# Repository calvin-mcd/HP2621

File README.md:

# HP2621

A pcb based on the HP2621 vintage home computer, supporting both MX and Alps switches and an extensive bottomrow.

Two case designs are being worked on by @obobobobo and fivedee.

## Layout

[Link](http://www.keyboard-layout-editor.com/#/gists/fb3fb2c8d70fd99746aac4b5d0be48f5)

## Pictures

The OG keyboard/computer inspiration

## Todo

- [ ] order & test pcb
- [ ] create firmware
- [ ] create & test cases

## Disclaimer

Please note that this project is a work in progress with no guarantees of a working outcome. No-one involved in this project is responsible for any usage issues that may arise. However, feel free to edit, modify and otherwise utilise these files.

## License

This project is released under the GPL v3 License. Please refer to the LICENCE file.

## Credits

Any questions, contact Calvin0563 on Discord.

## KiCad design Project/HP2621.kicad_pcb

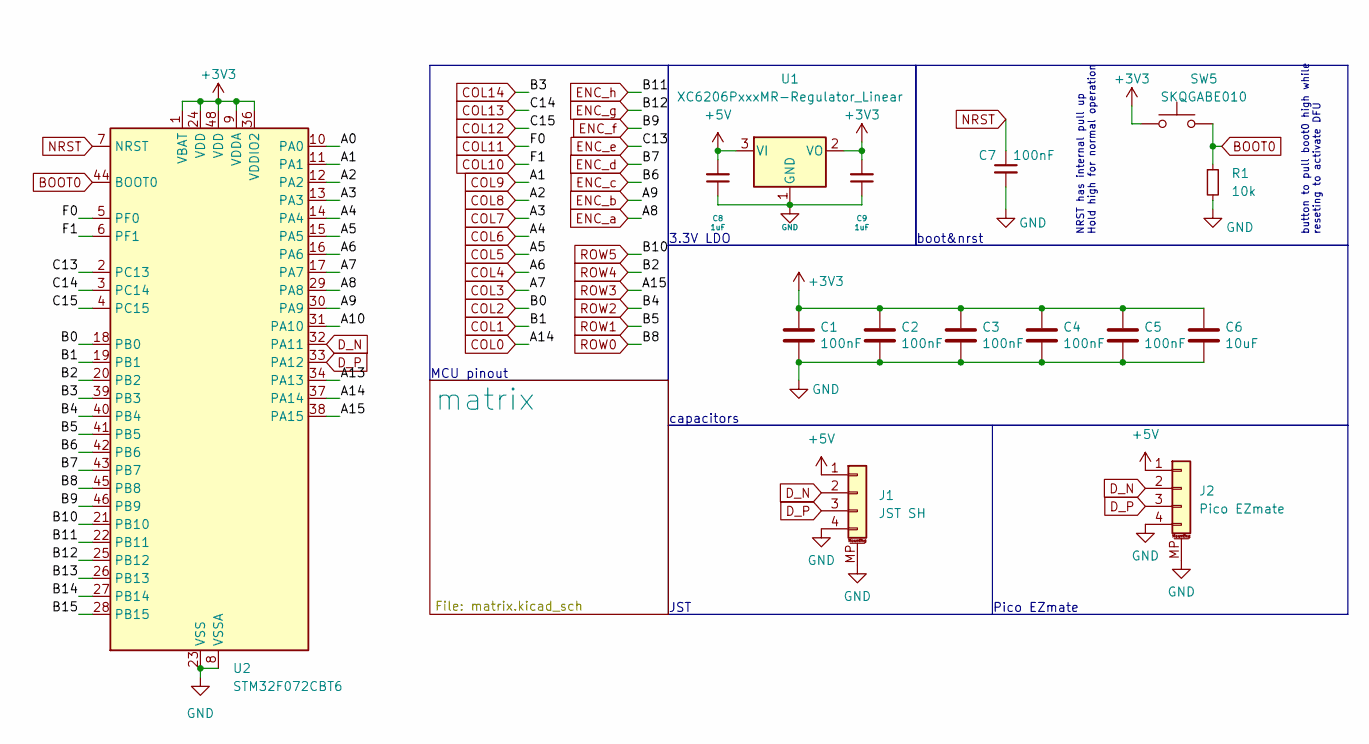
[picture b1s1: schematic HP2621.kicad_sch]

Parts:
C1, C2, C3, C4, C5, C7: 100nF; C_0402_1005Metric; LCSC C307331
C6: 10uF; C_0603_1608Metric
C8, C9: 1uF; C_0402_1005Metric; LCSC C52923
J1: JST SH; JST_SH_SM04B-SRSS-TB_1x04-1MP_P1.00mm_Horizontal
J2: Pico EZmate; Molex_Pico-EZmate_78171-0004_1x04-1MP_P1.20mm_Vertical
R1: 10k; R_0402_1005Metric
SW5: SKQGABE010; SW_SPST_SKQG_WithStem; LCSC C115351
U1: XC6206PxxxMR-Regulator_Linear; SOT-23; LCSC C5446
U2: STM32F072CBT6; LQFP-48_7x7mm_P0.5mm; JlcRotOffset 90

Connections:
+3V3: C1.1, C2.1, C3.1, C4.1, C5.1, C6.1, C9.2, SW5.1, U1.2 (VO), U2.1 (VBAT), U2.9 (VDDA), U2.24 (VDD), U2.36 (VDDIO2), U2.48 (VDD)
+5V: C8.2, J1.1, J2.1, U1.3 (VI)
/A0: U2.10 (PA0)
/A10: U2.31 (PA10)
/A13: U2.34 (PA13)
/B13: U2.26 (PB13)
/B14: U2.27 (PB14)
/B15: U2.28 (PB15)
BOOT0: R1.1, SW5.2, U2.44 (BOOT0)
COL0: U2.37 (PA14); also elsewhere on the board
COL1: U2.19 (PB1); also elsewhere on the board
COL2: U2.18 (PB0); also elsewhere on the board
COL3: U2.17 (PA7); also elsewhere on the board
COL4: U2.16 (PA6); also elsewhere on the board
COL5: U2.15 (PA5); also elsewhere on the board
COL6: U2.14 (PA4); also elsewhere on the board
COL7: U2.13 (PA3); also elsewhere on the board
COL8: U2.12 (PA2); also elsewhere on the board
COL9: U2.11 (PA1); also elsewhere on the board
COL10: U2.6 (PF1); also elsewhere on the board
COL11: U2.5 (PF0); also elsewhere on the board
COL12: U2.4 (PC15); also elsewhere on the board
COL13: U2.3 (PC14); also elsewhere on the board
COL14: U2.39 (PB3); also elsewhere on the board
D_N: J1.2, J2.2, U2.32 (PA11)
D_P: J1.3, J2.3, U2.33 (PA12)
ENC_a: U2.29 (PA8); also elsewhere on the board
ENC_b: U2.30 (PA9); also elsewhere on the board
ENC_c: U2.42 (PB6); also elsewhere on the board
ENC_d: U2.43 (PB7); also elsewhere on the board
ENC_e: U2.2 (PC13); also elsewhere on the board
ENC_f: U2.46 (PB9); also elsewhere on the board
ENC_g: U2.25 (PB12); also elsewhere on the board
ENC_h: U2.22 (PB11); also elsewhere on the board
GND: C1.2, C2.2, C3.2, C4.2, C5.2, C6.2, C7.2, C8.1, C9.1, J1.4, J1.MP (MountPin), J2.4, J2.MP (MountPin), R1.2, U1.1 (GND), U2.8 (VSSA), U2.23 (VSS), U2.35 (VSS), U2.47 (VSS); also elsewhere on the board
NRST: C7.1, U2.7 (NRST)
ROW0: U2.45 (PB8); also elsewhere on the board
ROW1: U2.41 (PB5); also elsewhere on the board
ROW2: U2.40 (PB4); also elsewhere on the board
ROW3: U2.38 (PA15); also elsewhere on the board
ROW4: U2.20 (PB2); also elsewhere on the board
ROW5: U2.21 (PB10); also elsewhere on the board

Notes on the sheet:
3.3V LDO
capacitors
NRST has internal pull up Hold high for normal operation
boot&nrst
MCU pinout
Pico EZmate
JST
button to pull boot0 high while reseting to activate DFU

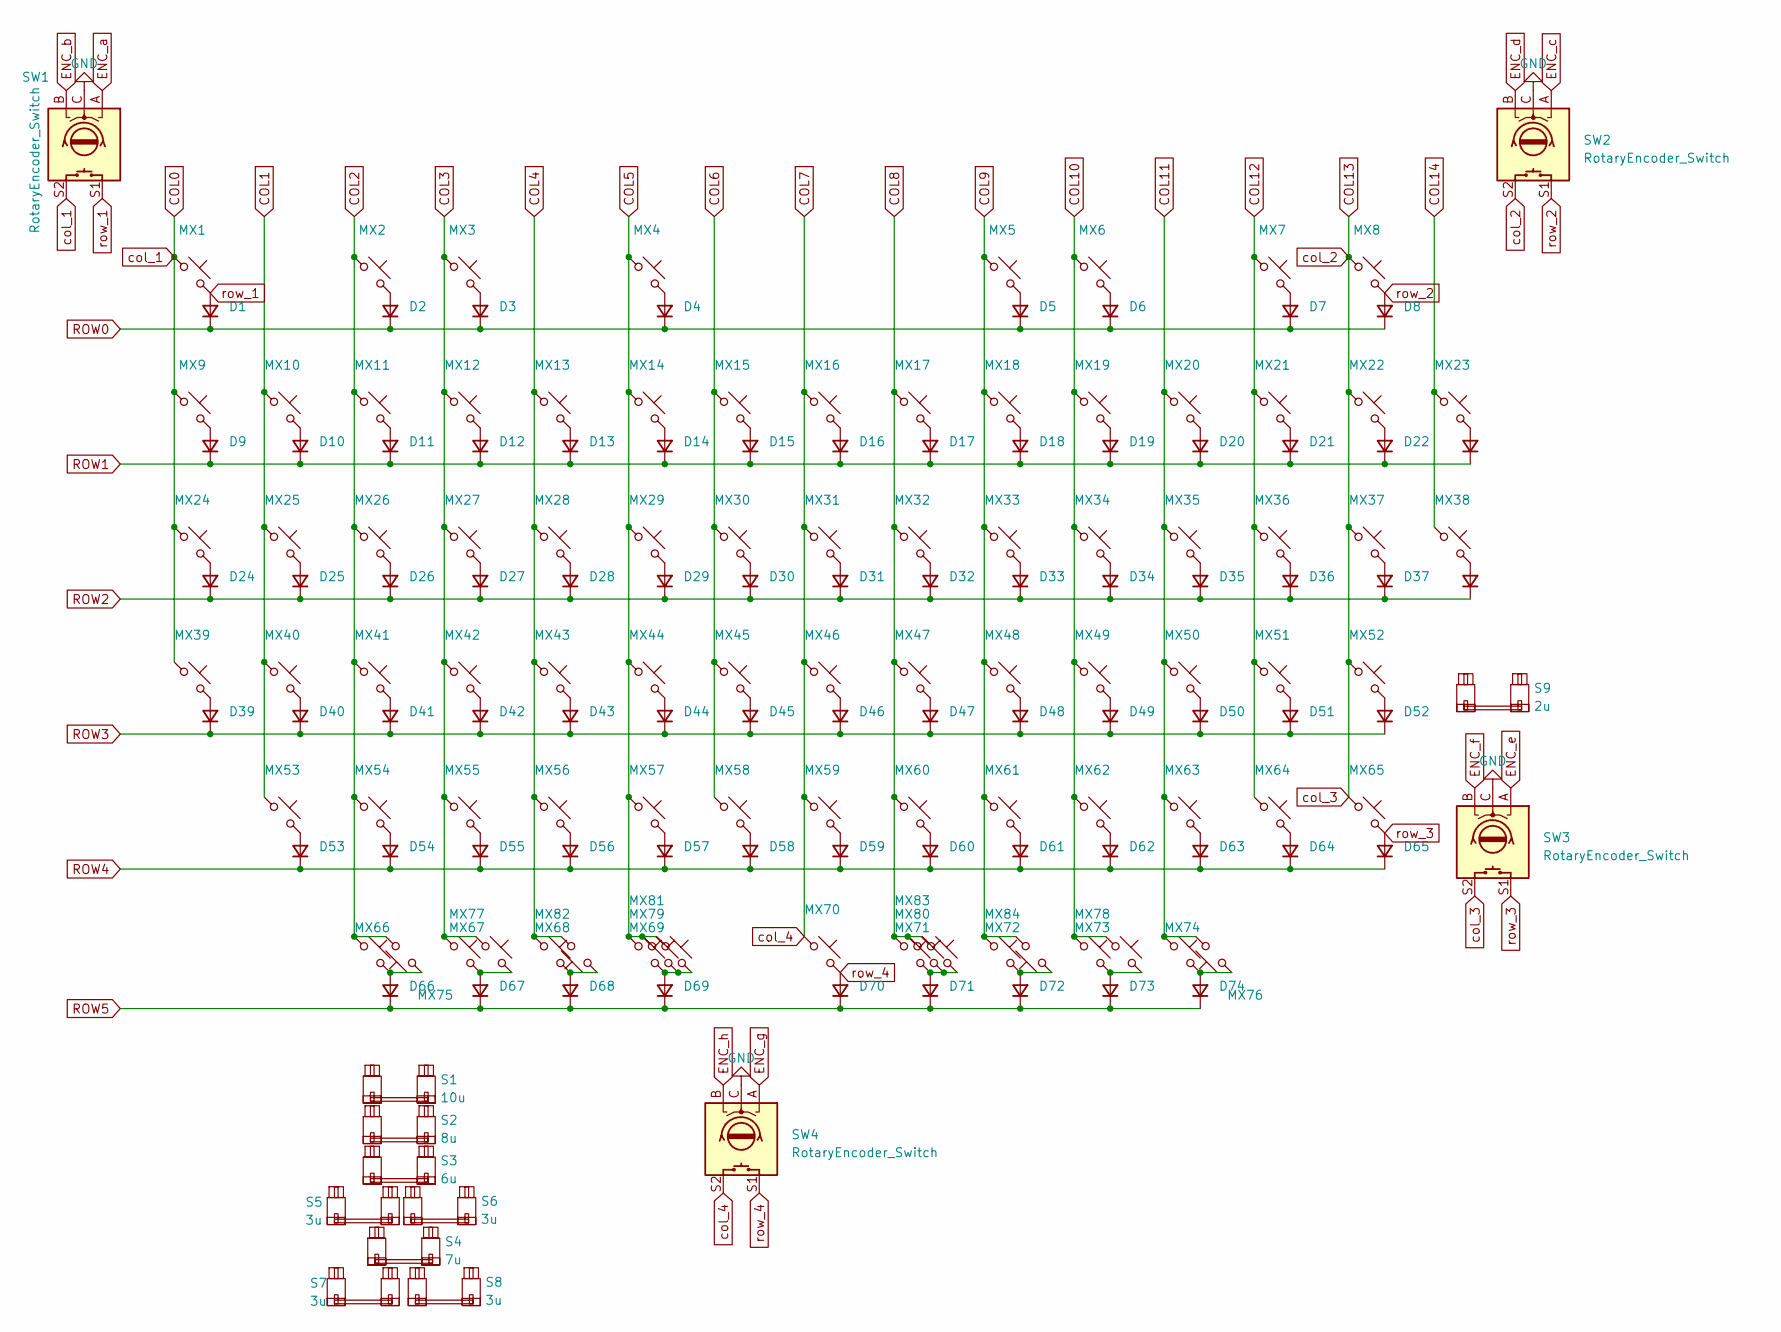
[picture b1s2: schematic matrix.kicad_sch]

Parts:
D1, D2, D3, D4, D5, D6, D7, D8, D9, D10, D11, D12, D13, D14, D15, D16, D17, D18, D19, D20, D21, D22, D23, D24, D25, D26, D27, D28, D29, D30, D31, D32, D33, D34, D35, D36, D37, D38, D39, D40, D41, D42, D43, D44, D45, D46, D47, D48, D49, D50, D51, D52, D53, D54, D55, D56, D57, D58, D59, D60, D61, D62, D63, D64, D65, D66, D67, D68, D69, D70, D71, D72, D73, D74: D_Small; D_SOD-123F
MX1, MX2, MX3, MX4, MX5, MX6, MX7, MX8, MX24, MX53, MX64, MX75, MX76: MX_SW_solder; SW_Alps_MX_1.5u
MX9, MX10, MX11, MX12, MX13, MX14, MX15, MX16, MX17, MX18, MX19, MX20, MX21, MX22, MX23, MX25, MX26, MX27, MX28, MX29, MX30, MX31, MX32, MX33, MX34, MX35, MX36, MX37, MX38, MX39, MX40, MX41, MX42, MX43, MX44, MX45, MX46, MX47, MX48, MX49, MX50, MX51, MX52, MX54, MX55, MX56, MX57, MX58, MX59, MX60, MX61, MX62, MX63, MX65, MX66, MX67, MX70, MX73, MX74, MX81, MX82, MX83, MX84: MX_SW_solder; SW_Alps_MX_1u
MX68, MX72, MX77, MX78: MX_SW_solder; SW_Alps_MX_1.25u
MX69, MX71, MX79, MX80: MX_SW_solder; SW_Alps_MX_1.75u
S1: 10u; STAB_MX_10u
S2: 8u; STAB_MX_8u
S3: 6u; STAB_MX_6u
S4: 7u; STAB_MX_7u
S5, S6, S7, S8: 3u; STAB_MX_3u
S9: 2u; STAB_MX_2u
SW1, SW2, SW3, SW4: RotaryEncoder_Switch; ROT_Alps_EC11E-Switch

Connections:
COL0: MX1.1, MX9.1, MX24.1, MX39.1, SW1.S2; also elsewhere on the board
COL1: MX10.1, MX25.1, MX40.1, MX53.1; also elsewhere on the board
COL2: MX2.1, MX11.1, MX26.1, MX41.1, MX54.1, MX66.1, MX75.2; also elsewhere on the board
COL3: MX3.1, MX12.1, MX27.1, MX42.1, MX55.1, MX67.1, MX77.1; also elsewhere on the board
COL4: MX13.1, MX28.1, MX43.1, MX56.1, MX68.1, MX82.2; also elsewhere on the board
COL5: MX4.1, MX14.1, MX29.1, MX44.1, MX57.1, MX69.1, MX79.1, MX81.1; also elsewhere on the board
COL6: MX15.1, MX30.1, MX45.1, MX58.1; also elsewhere on the board
COL7: MX16.1, MX31.1, MX46.1, MX59.1, MX70.1, SW4.S2; also elsewhere on the board
COL8: MX17.1, MX32.1, MX47.1, MX60.1, MX71.1, MX80.1, MX83.1; also elsewhere on the board
COL9: MX5.1, MX18.1, MX33.1, MX48.1, MX61.1, MX72.1, MX84.2; also elsewhere on the board
COL10: MX6.1, MX19.1, MX34.1, MX49.1, MX62.1, MX73.1, MX78.1; also elsewhere on the board
COL11: MX20.1, MX35.1, MX50.1, MX63.1, MX74.1, MX76.2; also elsewhere on the board
COL12: MX7.1, MX21.1, MX36.1, MX51.1, MX64.1; also elsewhere on the board
COL13: MX8.1, MX22.1, MX37.1, MX52.1, MX65.1, SW2.S2, SW3.S2; also elsewhere on the board
COL14: MX23.1, MX38.1; also elsewhere on the board
ENC_a: SW1.A; also elsewhere on the board
ENC_b: SW1.B; also elsewhere on the board
ENC_c: SW2.A; also elsewhere on the board
ENC_d: SW2.B; also elsewhere on the board
ENC_e: SW3.A; also elsewhere on the board
ENC_f: SW3.B; also elsewhere on the board
ENC_g: SW4.A; also elsewhere on the board
ENC_h: SW4.B; also elsewhere on the board
GND: SW1.C, SW2.C, SW3.C, SW4.C; also elsewhere on the board
unnamed: D2.2 (A), MX2.2
unnamed: D3.2 (A), MX3.2
unnamed: D4.2 (A), MX4.2
unnamed: D5.2 (A), MX5.2
unnamed: D6.2 (A), MX6.2
unnamed: D7.2 (A), MX7.2
unnamed: D9.2 (A), MX9.2
unnamed: D10.2 (A), MX10.2
unnamed: D11.2 (A), MX11.2
unnamed: D12.2 (A), MX12.2
unnamed: D13.2 (A), MX13.2
unnamed: D14.2 (A), MX14.2
unnamed: D15.2 (A), MX15.2
unnamed: D16.2 (A), MX16.2
unnamed: D17.2 (A), MX17.2
unnamed: D18.2 (A), MX18.2
unnamed: D19.2 (A), MX19.2
unnamed: D20.2 (A), MX20.2
unnamed: D21.2 (A), MX21.2
unnamed: D22.2 (A), MX22.2
unnamed: D23.2 (A), MX23.2
unnamed: D24.2 (A), MX24.2
unnamed: D25.2 (A), MX25.2
unnamed: D26.2 (A), MX26.2
unnamed: D27.2 (A), MX27.2
unnamed: D28.2 (A), MX28.2
unnamed: D29.2 (A), MX29.2
unnamed: D30.2 (A), MX30.2
unnamed: D31.2 (A), MX31.2
unnamed: D32.2 (A), MX32.2
unnamed: D33.2 (A), MX33.2
unnamed: D34.2 (A), MX34.2
unnamed: D35.2 (A), MX35.2
unnamed: D36.2 (A), MX36.2
unnamed: D37.2 (A), MX37.2
unnamed: D38.2 (A), MX38.2
unnamed: D39.2 (A), MX39.2
unnamed: D40.2 (A), MX40.2
unnamed: D41.2 (A), MX41.2
unnamed: D42.2 (A), MX42.2
unnamed: D43.2 (A), MX43.2
unnamed: D44.2 (A), MX44.2
unnamed: D45.2 (A), MX45.2
unnamed: D46.2 (A), MX46.2
unnamed: D47.2 (A), MX47.2
unnamed: D48.2 (A), MX48.2
unnamed: D49.2 (A), MX49.2
unnamed: D50.2 (A), MX50.2
unnamed: D51.2 (A), MX51.2
unnamed: D52.2 (A), MX52.2
unnamed: D53.2 (A), MX53.2
unnamed: D54.2 (A), MX54.2
unnamed: D55.2 (A), MX55.2
unnamed: D56.2 (A), MX56.2
unnamed: D57.2 (A), MX57.2
unnamed: D58.2 (A), MX58.2
unnamed: D59.2 (A), MX59.2
unnamed: D60.2 (A), MX60.2
unnamed: D61.2 (A), MX61.2
unnamed: D62.2 (A), MX62.2
unnamed: D63.2 (A), MX63.2
unnamed: D64.2 (A), MX64.2
unnamed: D66.2 (A), MX66.2, MX75.1
unnamed: D67.2 (A), MX67.2, MX77.2
unnamed: D68.2 (A), MX68.2, MX82.1
unnamed: D69.2 (A), MX69.2, MX79.2, MX81.2
unnamed: D71.2 (A), MX71.2, MX80.2, MX83.2
unnamed: D72.2 (A), MX72.2, MX84.1
unnamed: D73.2 (A), MX73.2, MX78.2
unnamed: D74.2 (A), MX74.2, MX76.1
ROW0: D1.1 (K), D2.1 (K), D3.1 (K), D4.1 (K), D5.1 (K), D6.1 (K), D7.1 (K), D8.1 (K); also elsewhere on the board
ROW1: D9.1 (K), D10.1 (K), D11.1 (K), D12.1 (K), D13.1 (K), D14.1 (K), D15.1 (K), D16.1 (K), D17.1 (K), D18.1 (K), D19.1 (K), D20.1 (K), D21.1 (K), D22.1 (K), D23.1 (K); also elsewhere on the board
ROW2: D24.1 (K), D25.1 (K), D26.1 (K), D27.1 (K), D28.1 (K), D29.1 (K), D30.1 (K), D31.1 (K), D32.1 (K), D33.1 (K), D34.1 (K), D35.1 (K), D36.1 (K), D37.1 (K), D38.1 (K); also elsewhere on the board
ROW3: D39.1 (K), D40.1 (K), D41.1 (K), D42.1 (K), D43.1 (K), D44.1 (K), D45.1 (K), D46.1 (K), D47.1 (K), D48.1 (K), D49.1 (K), D50.1 (K), D51.1 (K), D52.1 (K); also elsewhere on the board
ROW4: D53.1 (K), D54.1 (K), D55.1 (K), D56.1 (K), D57.1 (K), D58.1 (K), D59.1 (K), D60.1 (K), D61.1 (K), D62.1 (K), D63.1 (K), D64.1 (K), D65.1 (K); also elsewhere on the board
ROW5: D66.1 (K), D67.1 (K), D68.1 (K), D69.1 (K), D70.1 (K), D71.1 (K), D72.1 (K), D73.1 (K), D74.1 (K); also elsewhere on the board
row_1: D1.2 (A), MX1.2, SW1.S1
row_2: D8.2 (A), MX8.2, SW2.S1
row_3: D65.2 (A), MX65.2, SW3.S1
row_4: D70.2 (A), MX70.2, SW4.S1

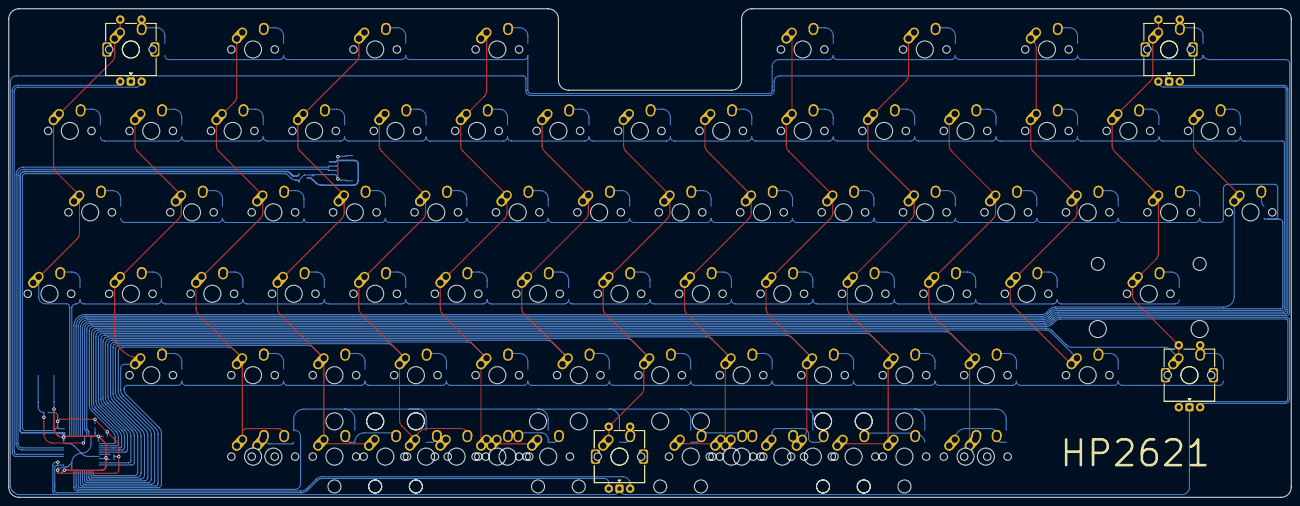
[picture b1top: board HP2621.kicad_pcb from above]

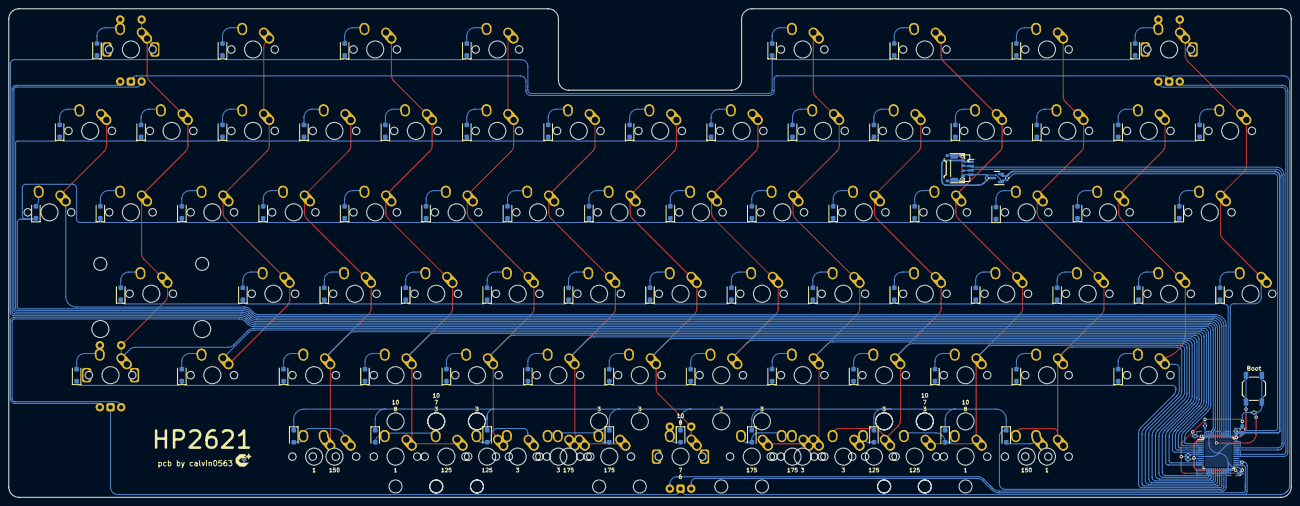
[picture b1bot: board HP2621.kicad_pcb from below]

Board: 2 copper layers, 300.0 x 114.3 mm, 184 parts (89 on the bottom side), 110 nets.

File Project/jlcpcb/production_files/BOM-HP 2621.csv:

Comment,Designator,Footprint,LCSC
SKQGABE010,SW5,SW_SPST_SKQG_WithStem,C115351
10k,R1,R_0402_1005Metric,C25744
100nF,"C1,C2,C3,C4,C5,C7",C_0402_1005Metric,C307331
1uF,"C8,C9",C_0402_1005Metric,C52923
XC6206PxxxMR-Regulator_Linear,U1,SOT-23,C5446
Pico EZmate,J2,Molex_Pico-EZmate_78171-0004_1x04-1MP_P1.20mm_Vertical,C588524
D_Small,"D1,D10,D11,D12,D13,D14,D15,D16,D17,D18,D19,D2,D20,D21,D22,D23,D24,D25,D26,D27,D28,D29,D3,D30,D31,D32,D33,D34,D35,D36,D37,D38,D39,D4,D40,D41,D42,D43,D44,D45,D46,D47,D48,D49,D5,D50,D51,D52,D53,D54,D55,D56,D57,D58,D59,D6,D60,D61,D62,D63,D64,D65,D66,D67,D68,D69,D7,D70,D71,D72,D73,D74,D8,D9",D_SOD-123F,C81598
STM32F072CBT6,U2,LQFP-48_7x7mm_P0.5mm,C81720
10uF,C6,C_0603_1608Metric,C96446

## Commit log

2024-01-04 readme
2024-01-04 silkscreen correction, fresh gerbers
2024-01-09 backup
2024-01-31 fresh gerbers
